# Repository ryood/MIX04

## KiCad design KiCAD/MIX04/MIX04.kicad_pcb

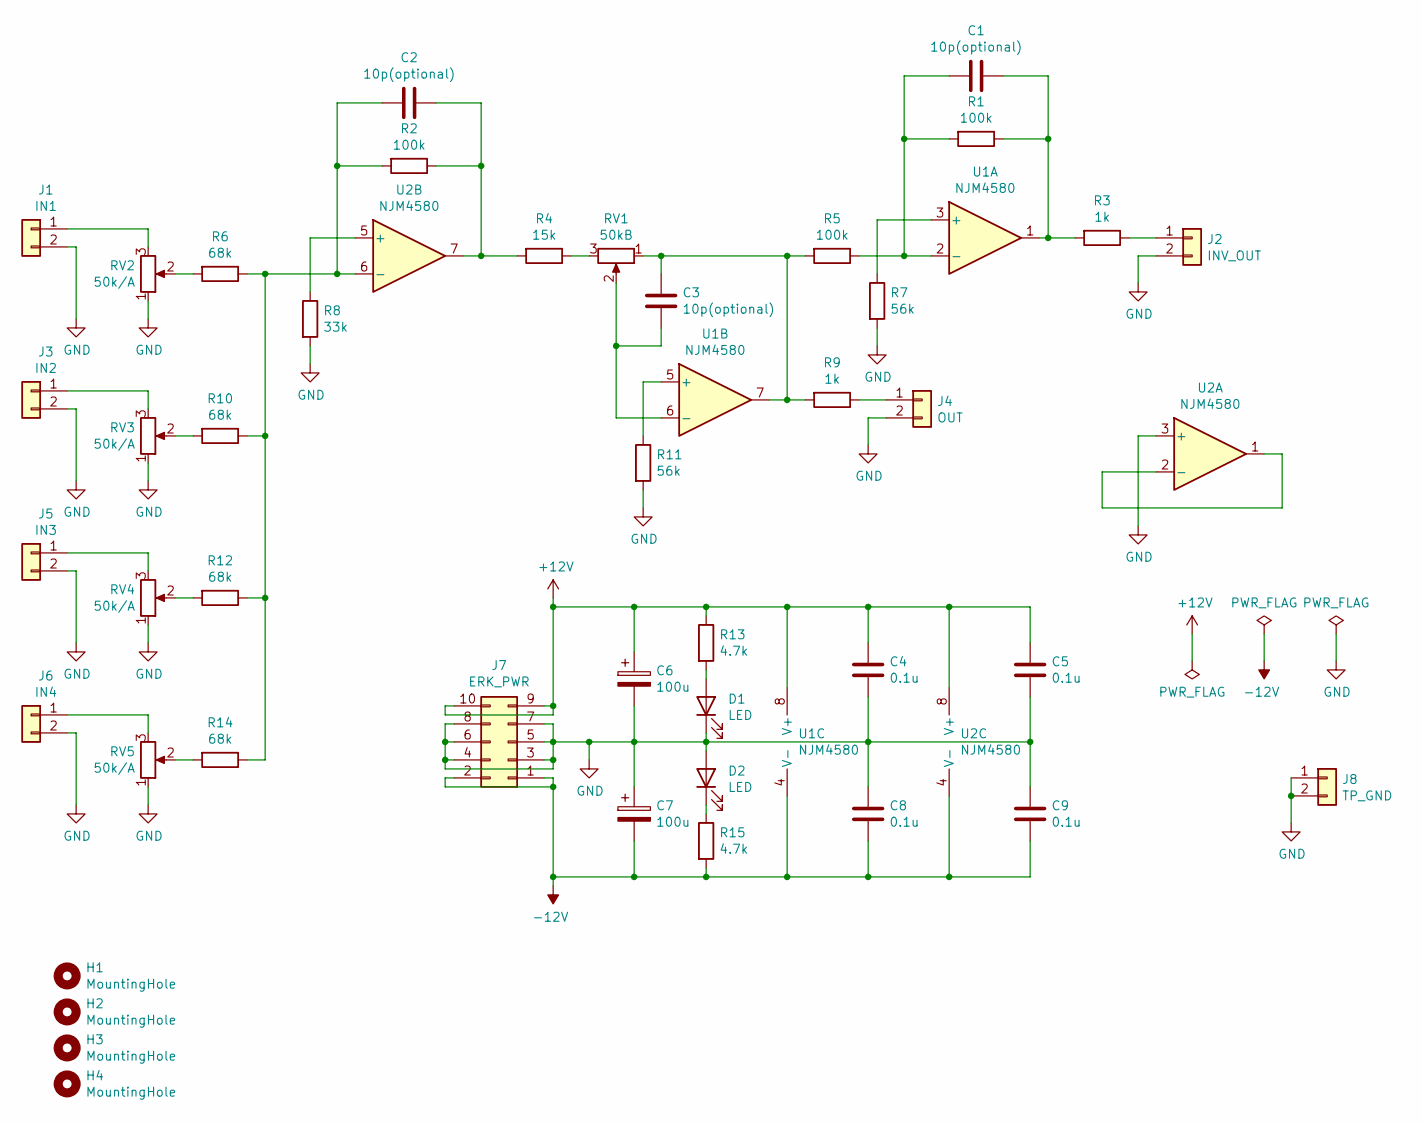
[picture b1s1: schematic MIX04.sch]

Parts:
C1, C2, C3: 10p(optional); C_Disc_D3.0mm_W2.0mm_P2.50mm
C4, C5: 0.1u; C_Disc_D3.4mm_W2.1mm_P2.50mm
C6, C7: 100u; CP_Radial_D6.3mm_P2.50mm
C8, C9: 0.1u; C_Disc_D3.0mm_W2.0mm_P2.50mm
D1, D2: LED; LED_D3.0mm
H1, H2, H3, H4: MountingHole; MountingHole_3.2mm_M3
J1: IN1; JST_XH_B2B-XH-A_1x02_P2.50mm_Vertical
J2: INV_OUT; JST_XH_B2B-XH-A_1x02_P2.50mm_Vertical
J3: IN2; JST_XH_B2B-XH-A_1x02_P2.50mm_Vertical
J4: OUT; JST_XH_B2B-XH-A_1x02_P2.50mm_Vertical
J5: IN3; JST_XH_B2B-XH-A_1x02_P2.50mm_Vertical
J6: IN4; JST_XH_B2B-XH-A_1x02_P2.50mm_Vertical
J7: ERK_PWR; IDC-Header_2x05_P2.54mm_Vertical
J8: TP_GND; PinHeader_1x02_P2.54mm_Vertical
R1, R2, R5: 100k; R_Axial_DIN0207_L6.3mm_D2.5mm_P10.16mm_Horizontal
R3, R9: 1k; R_Axial_DIN0207_L6.3mm_D2.5mm_P10.16mm_Horizontal
R4: 15k; R_Axial_DIN0207_L6.3mm_D2.5mm_P10.16mm_Horizontal
R6, R10, R12, R14: 68k; R_Axial_DIN0207_L6.3mm_D2.5mm_P10.16mm_Horizontal
R7, R11: 56k; R_Axial_DIN0207_L6.3mm_D2.5mm_P10.16mm_Horizontal
R8: 33k; R_Axial_DIN0207_L6.3mm_D2.5mm_P10.16mm_Horizontal
R13, R15: 4.7k; R_Axial_DIN0207_L6.3mm_D2.5mm_P10.16mm_Horizontal
RV1: 50kB; Potentiometer_Alps_RK097_Single_Horizontal
RV2, RV3, RV4, RV5: 50k/A; Potentiometer_Alps_RK097_Single_Horizontal
U1, U2: NJM4580; DIP-8_W7.62mm_Socket_LongPads

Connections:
+12V: C4.2, C5.2, C6.1, J7.9, J7.10, R13.1, U1.8 (V+), U2.8 (V+)
-12V: C7.2, C8.1, C9.1, J7.1, J7.2, R15.2, U1.4 (V-), U2.4 (V-)
GND: C4.1, C5.1, C6.2, C7.1, C8.2, C9.2, D1.1 (K), D2.2 (A), J1.2, J2.2, J3.2, J4.2, J5.2, J6.2, J7.3, J7.4, J7.5, J7.6, J7.7, J7.8, J8.1, J8.2, R7.2, R8.2, R11.2, RV2.1, RV3.1, RV4.1, RV5.1, U2.3 (+)
unnamed: C1.1, R1.1, R3.2, U1.1
unnamed: C1.2, R1.2, R5.1, U1.2 (-)
unnamed: C2.1, R2.1, R4.2, U2.7
unnamed: C2.2, R2.2, R6.1, R10.1, R12.1, R14.1, U2.6 (-)
unnamed: C3.1, R5.2, R9.2, RV1.1, U1.7
unnamed: C3.2, RV1.2, U1.6 (-)
unnamed: D1.2 (A), R13.2
unnamed: D2.1 (K), R15.1
unnamed: J1.1, RV2.3
unnamed: J2.1, R3.1
unnamed: J3.1, RV3.3
unnamed: J4.1, R9.1
unnamed: J5.1, RV4.3
unnamed: J6.1, RV5.3
unnamed: R4.1, RV1.3
unnamed: R6.2, RV2.2
unnamed: R7.1, U1.3 (+)
unnamed: R8.1, U2.5 (+)
unnamed: R10.2, RV3.2
unnamed: R11.1, U1.5 (+)
unnamed: R12.2, RV4.2
unnamed: R14.2, RV5.2
unnamed: U2.1, U2.2 (-)

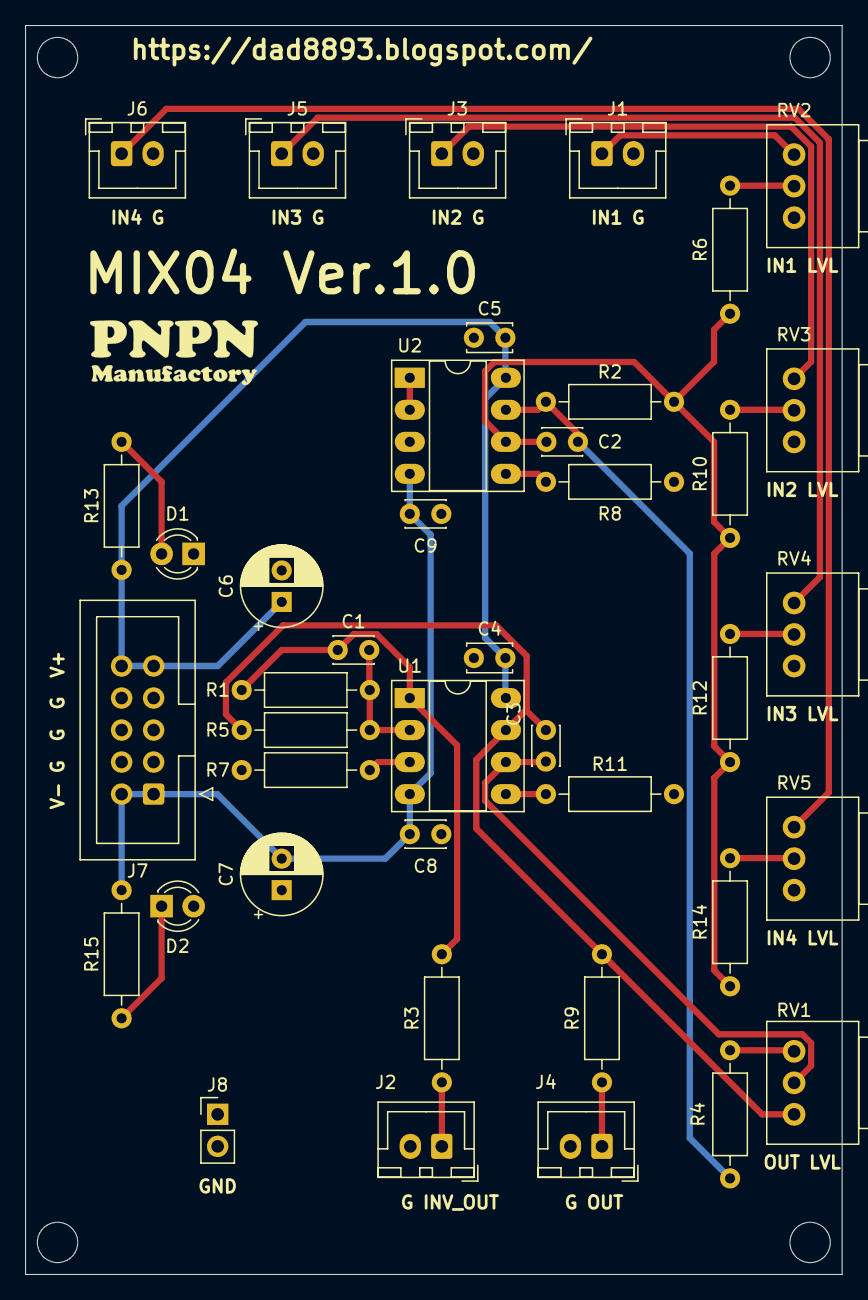
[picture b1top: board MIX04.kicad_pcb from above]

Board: 2 copper layers, 64.8 x 99.1 mm, 45 parts (0 on the bottom side), 26 nets.

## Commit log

2021-07-01 Board design
2021-08-14 Panel design
2022-04-18 tidyup
